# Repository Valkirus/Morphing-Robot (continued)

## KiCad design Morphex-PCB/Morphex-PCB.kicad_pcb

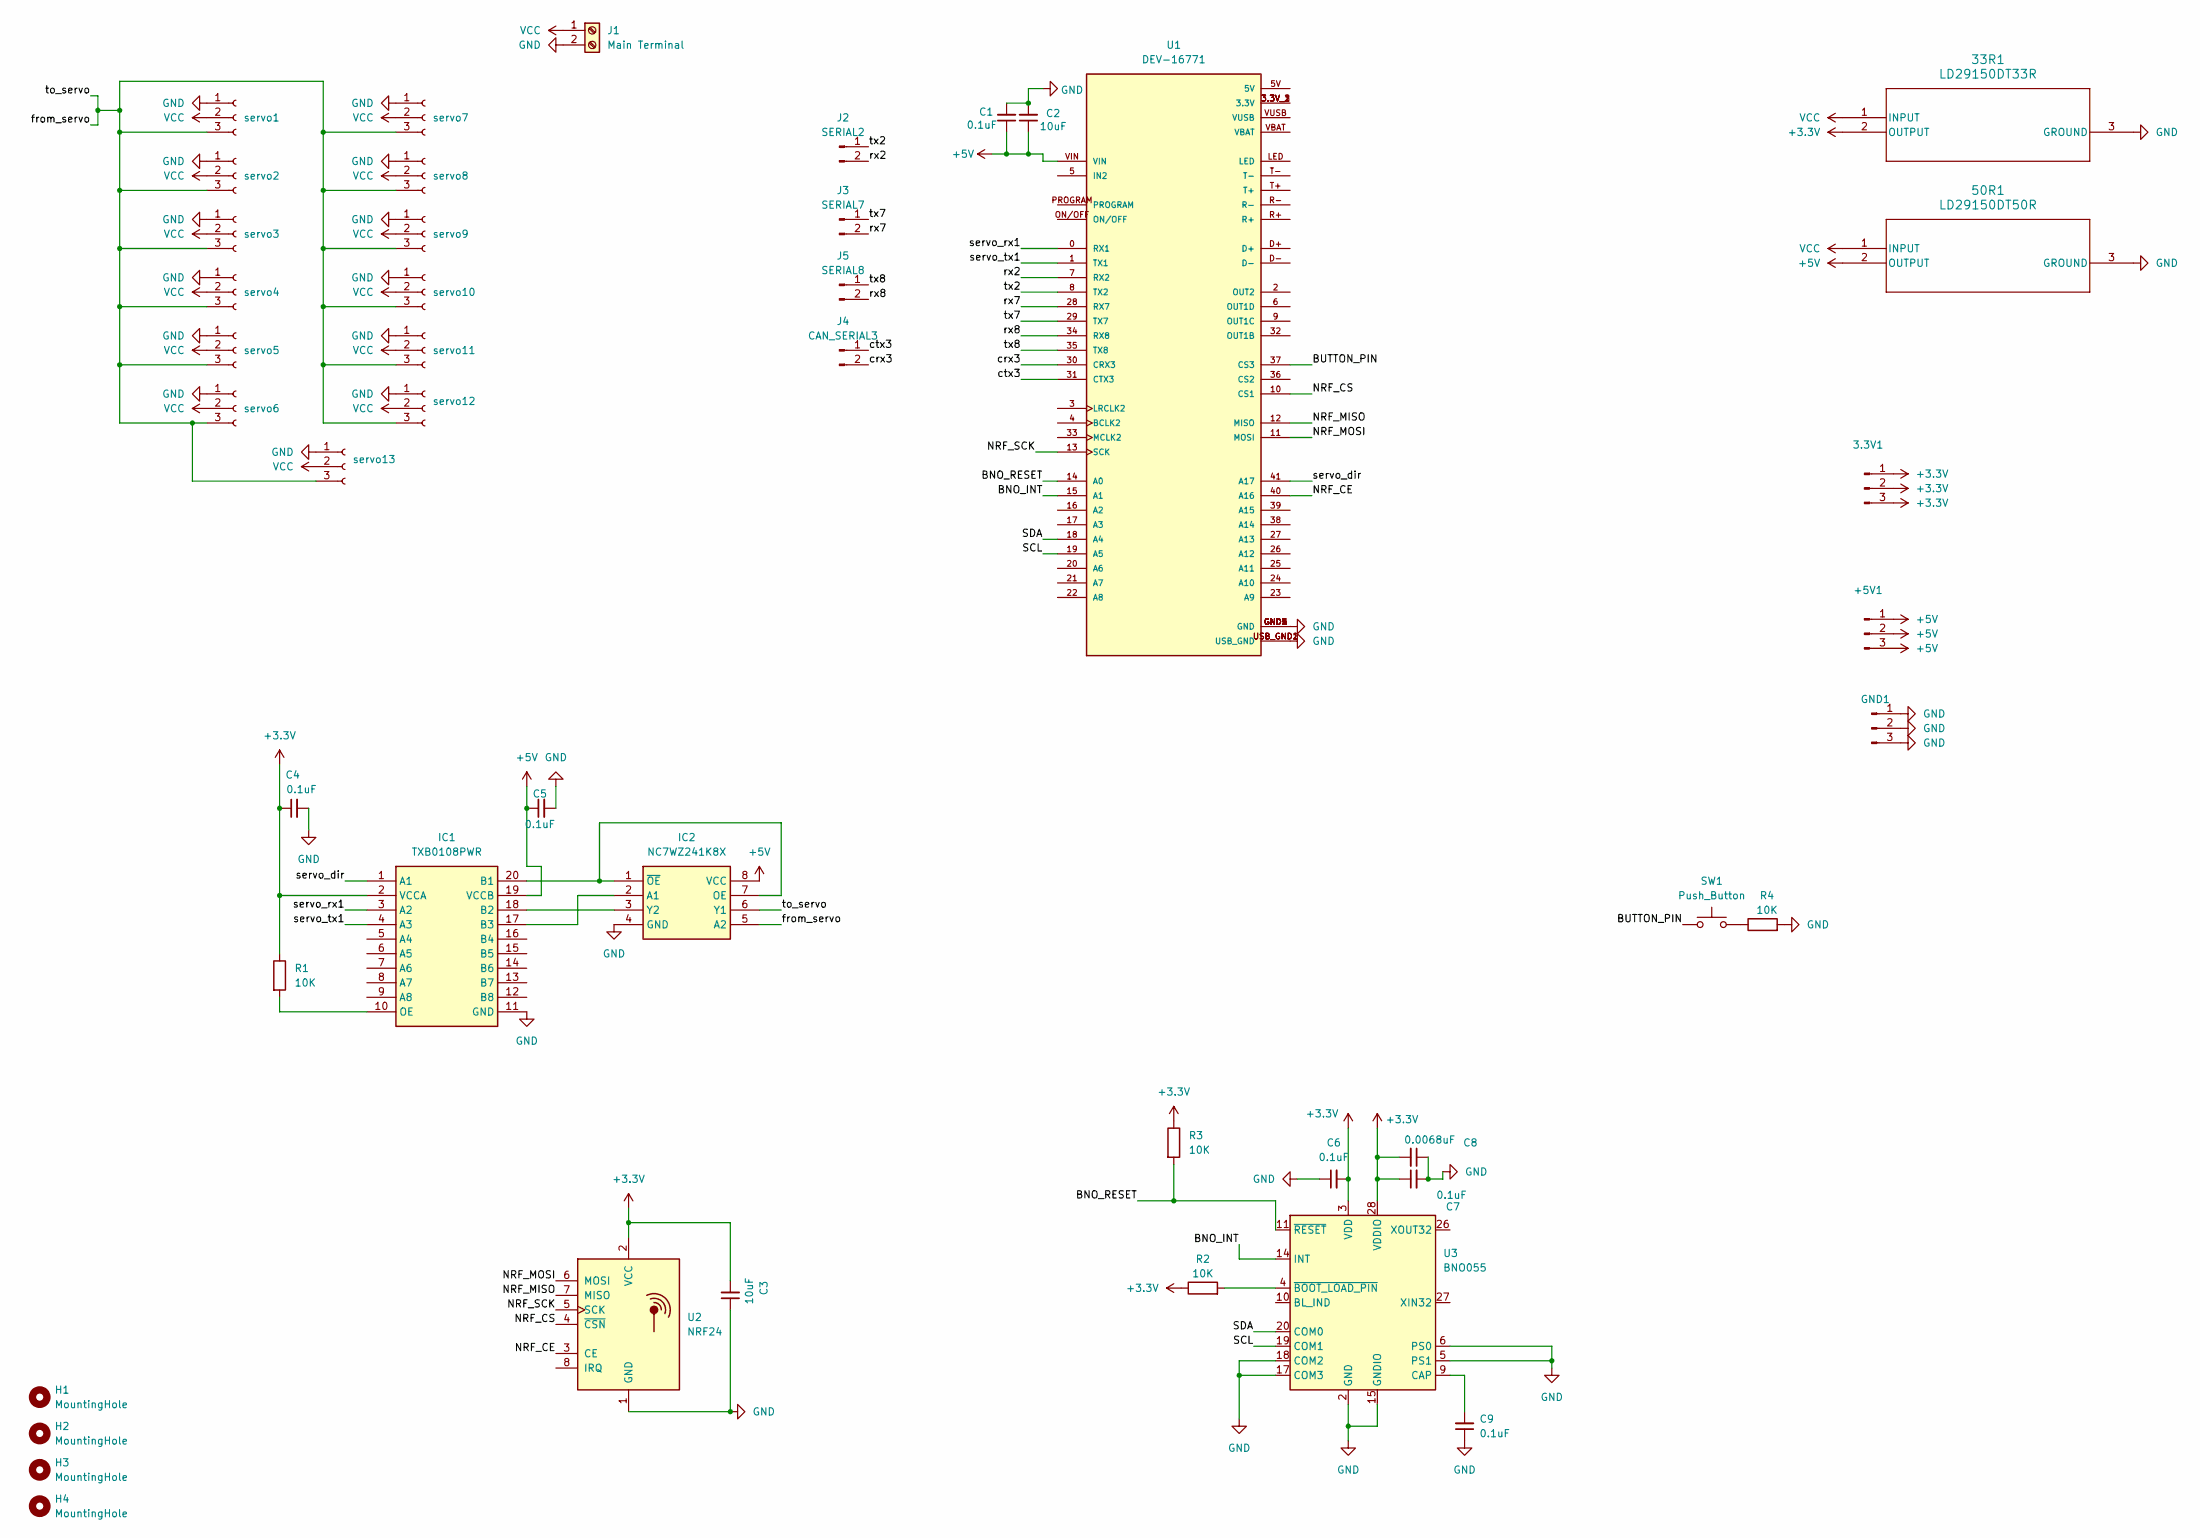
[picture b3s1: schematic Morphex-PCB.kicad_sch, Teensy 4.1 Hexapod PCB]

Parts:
3.3V1: Conn_01x03_Pin; PinHeader_1x03_P2.54mm_Vertical
33R1: LD29150DT33R; DPAK_STM
50R1: LD29150DT50R; DPAK_STM
+5V1: Conn_01x03_Pin; PinHeader_1x03_P2.54mm_Vertical
C1, C4, C5, C6, C7, C9: 0.1uF; C_0603_1608Metric_Pad1.08x0.95mm_HandSolder
C2, C3: 10uF; C_0805_2012Metric_Pad1.18x1.45mm_HandSolder
C8: 0.0068uF; C_0603_1608Metric_Pad1.08x0.95mm_HandSolder
GND1: Conn_01x03_Pin; PinHeader_1x03_P2.54mm_Vertical
H1, H2, H3, H4: MountingHole; MountingHole_3.2mm_M3
IC1: TXB0108PWR; SOP65P640X120-20N; Mouser Part Number 595-TXB0108PWR
IC2: NC7WZ241K8X; SOP50P310X90-8N; Mouser Part Number 512-NC7WZ241K8X
J1: Main Terminal; TerminalBlock_Phoenix_MKDS-1,5-2-5.08_1x02_P5.08mm_Horizont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
J2: SERIAL2; PinHeader_1x02_P2.54mm_Vertical
J3: SERIAL7; PinHeader_1x02_P2.54mm_Vertical
J4: CAN_SERIAL3; PinHeader_1x02_P2.54mm_Vertical
J5: SERIAL8; PinHeader_1x02_P2.54mm_Vertical
R1, R2, R3, R4: 10K; R_0603_1608Metric_Pad0.98x0.95mm_HandSolder
SW1: Push_Button; SW_PUSH_6mm
U1: DEV-16771; MODULE_DEV-16771; PARTREV 4.1
U2: NRF24; nRF24L01_Breakout
U3: BNO055; LGA-28_5.2x3.8mm_P0.5mm
servo1, servo2, servo3, servo4, servo5, servo6, servo7, servo8, servo9, servo10, servo11, servo12, servo13: Conn_01x03_Socket; JST_PH_B3B-PH-K_1x03_P2.00mm_Vertical

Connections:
+3.3V: 3.3V1.1, 3.3V1.2, 3.3V1.3, 33R1.2 (OUTPUT), C3.2, C4.1, C6.2, C7.1, C8.2, IC1.2 (VCCA), R1.1, R2.1, R3.1, U2.2 (VCC), U3.3 (VDD), U3.28 (VDDIO); also elsewhere on the board
+5V: 50R1.2 (OUTPUT), +5V1.1, +5V1.2, +5V1.3, C1.1, C2.1, C5.1, IC1.19 (VCCB), IC2.8 (VCC), U1.VIN; also elsewhere on the board
/BNO_INT: U1.15 (A1), U3.14 (INT)
/BNO_RESET: R3.2, U1.14 (A0), U3.11 (~RESET)
/BUTTON_PIN: SW1.1, U1.37 (CS3)
/NRF_CE: U1.40 (A16), U2.3 (CE)
/NRF_CS: U1.10 (CS1), U2.4 (~CSN)
/NRF_MISO: U1.12 (MISO), U2.7 (MISO)
/NRF_MOSI: U1.11 (MOSI), U2.6 (MOSI)
/NRF_SCK: U1.13 (SCK), U2.5 (SCK)
/SCL: U1.19 (A5), U3.19 (COM1)
/SDA: U1.18 (A4), U3.20 (COM0)
/crx3: J4.2, U1.30 (CRX3)
/ctx3: J4.1, U1.31 (CTX3)
/from_servo: IC2.5 (A2), IC2.6 (Y1), servo1.3, servo2.3, servo3.3, servo4.3, servo5.3, servo6.3, servo7.3, servo8.3, servo9.3, servo10.3, servo11.3, servo12.3, servo13.3
/rx2: J2.2, U1.7 (RX2)
/rx7: J3.2, U1.28 (RX7)
/rx8: J5.2, U1.34 (RX8)
/servo_dir: IC1.1 (A1), U1.41 (A17)
/servo_rx1: IC1.3 (A2), U1.0 (RX1)
/servo_tx1: IC1.4 (A3), U1.1 (TX1)
/tx2: J2.1, U1.8 (TX2)
/tx7: J3.1, U1.29 (TX7)
/tx8: J5.1, U1.35 (TX8)
GND: 33R1.3 (GROUND), 50R1.3 (GROUND), C1.2, C2.2, C3.1, C4.2, C5.2, C6.1, C7.2, C8.1, C9.1, GND1.1, GND1.2, GND1.3, IC1.11 (GND), IC2.4 (GND), J1.2, R4.2, U1.GND1 (GND), U1.GND2 (GND), U1.GND3 (GND), U1.GND4 (GND), U1.GND5 (GND), U1.USB_GND1 (USB_GND), U1.USB_GND2 (USB_GND), U2.1 (GND), U3.2 (GND), U3.5 (PS1), U3.6 (PS0), U3.15 (GNDIO), U3.16 (GNDIO), U3.17 (COM3), U3.18 (COM2), U3.25 (GNDIO), servo1.1, servo2.1, servo3.1, servo4.1, servo5.1, servo6.1, servo7.1, servo8.1, servo9.1, servo10.1, servo11.1, servo12.1, servo13.1; also elsewhere on the board
unnamed: IC1.20 (B1), IC2.1 (~OE), IC2.7 (OE)
unnamed: IC1.18 (B2), IC2.3 (Y2)
unnamed: IC1.17 (B3), IC2.2 (A1)
unnamed: IC1.10 (OE), R1.2
unnamed: R4.1, SW1.2
unnamed: U1.3.3V_1 (3.3V), U1.3.3V_2 (3.3V), U1.3.3V_3 (3.3V)
unnamed: C9.2, U3.9 (CAP)
unnamed: R2.2, U3.4 (~BOOT_LOAD_PIN)
VCC: 33R1.1 (INPUT), 50R1.1 (INPUT), J1.1, servo1.2, servo2.2, servo3.2, servo4.2, servo5.2, servo6.2, servo7.2, servo8.2, servo9.2, servo10.2, servo11.2, servo12.2, servo13.2; also elsewhere on the board

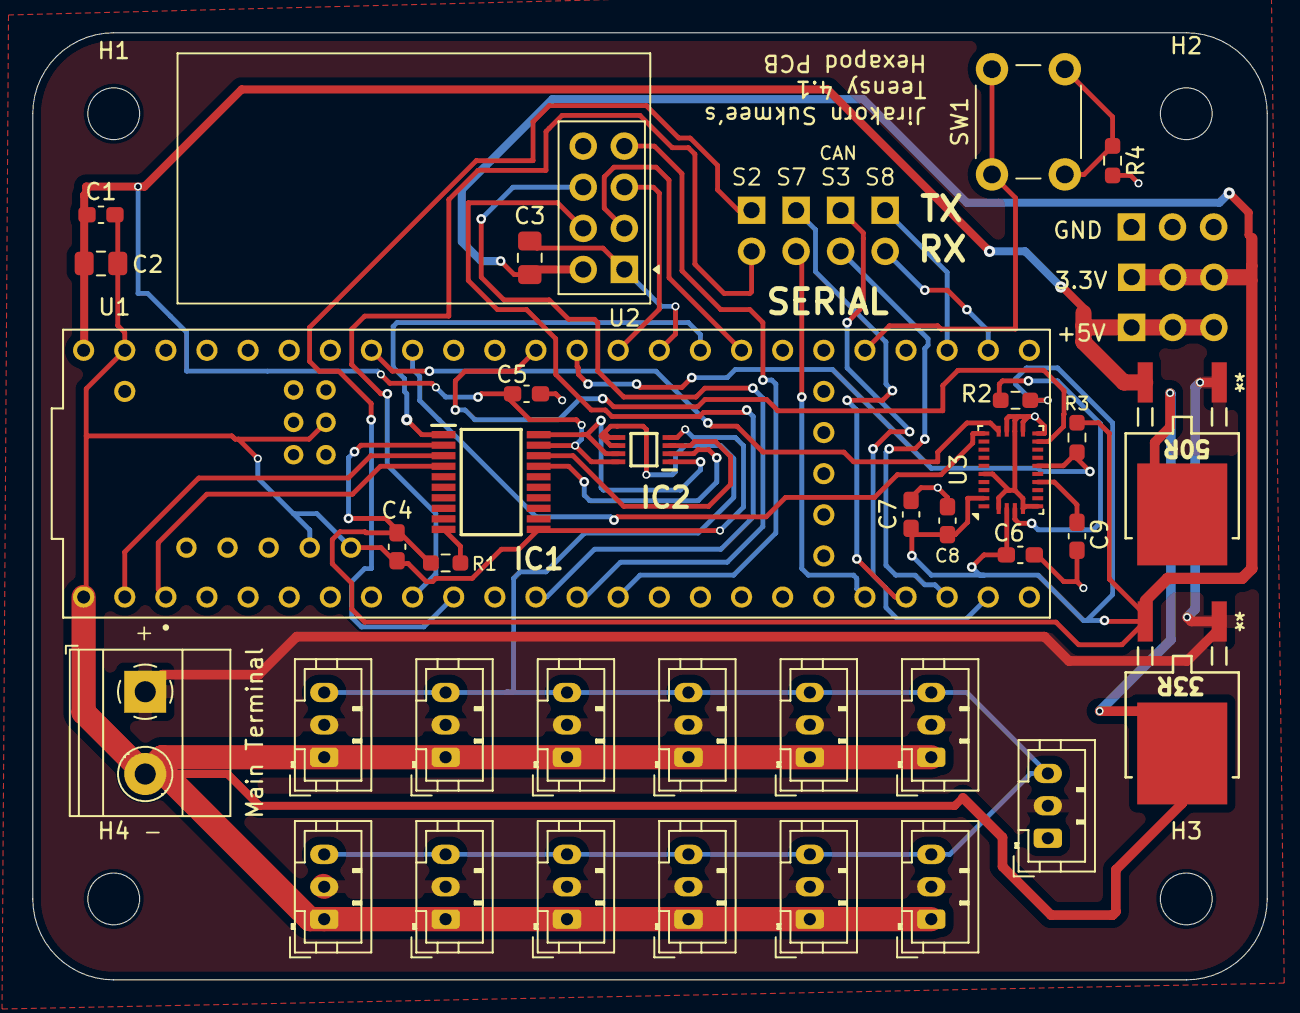
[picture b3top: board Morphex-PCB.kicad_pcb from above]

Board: 4 copper layers, 76.2 x 58.5 mm, 46 parts (0 on the bottom side), 34 nets.

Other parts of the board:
3.3V: Conn_01x03_Pin; PinHeader_1x03_P2.54mm_Vertical
+5V: Conn_01x03_Pin; PinHeader_1x03_P2.54mm_Vertical
GND: Conn_01x03_Pin; PinHeader_1x03_P2.54mm_Vertical
Main Terminal: Main Terminal; TerminalBlock_Phoenix_MKDS-1,5-2-5.08_1x02_P5.08mm_Horizont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

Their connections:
+3.3V: 3.3V.1, 3.3V.2, 3.3V.3; also elsewhere on the board
+5V: +5V.1, +5V.2, +5V.3; also elsewhere on the board
GND: GND.1, GND.2, GND.3, Main Terminal.2; also elsewhere on the board
VCC: Main Terminal.1; also elsewhere on the board

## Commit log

2024-12-14 added solidwork files
2024-12-15 15/12/2024
2024-12-17 reworked
2024-12-17 changed pictures
2024-12-20 updated 20/12/2024
2024-12-24 added pcb
2024-12-24 update pcb
2024-12-24 updated pcb
2024-12-25 fixed PCB
2024-12-26 added new pcb
2024-12-26 updated teensy's PCB
2024-12-29 not quite sure tbh
2025-01-05 added some new stuff
2025-01-12 PCB V0.2
2025-01-12 updated the PCB 13/01
2025-01-13 updated some stuff on the PCB
2025-01-16 I don't remember
2025-01-16 test
2025-01-17 small changes to the PCB
2025-01-17 removed some backups
2025-01-17 updated picutes
2025-01-17 removed some stuff
2025-01-19 updated the pcb
2025-01-19 changed some stuff
2025-01-26 updated pcb: changed from nrf24l01 to lora ra-02
2025-01-27 removed PCBs and create a new respiratory
